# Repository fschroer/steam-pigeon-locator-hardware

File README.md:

# Steam Pigeon locator hardware

KiCad 10 design for the Steam Pigeon rocket locator: an STM32WL5MOC LoRa module with GPS, IMU, barometer, flash, USB-C charging and four deployment channels. Firmware lives in [steam-pigeon-locator](https://github.com/fschroer/steam-pigeon-locator).

## Board at a glance

| Block | Parts |
| --- | --- |
| MCU and radio | STM32WL5MOCH6TR (U5), U.FL antenna (J7), high-power PA configuration |
| GPS | u-blox SAM-M10Q (U2), I2C2 at 0x42 |
| Sensors | ISM6HG256X IMU (U14), MS5611 barometer (U16), MX25L6436F flash (U17), all on SPI2 |
| Power | BQ25185 charger (U18), RT9080-33 LDO (U7), DRV5032 Hall sensor and 74HCS00 latch for magnet on/off |
| USB | USB-C (J1), CH340N serial (U4) |
| Deployment | Arm switch U13 (DMP2021UFDF) driven by DARM, four TPS22950 high-side switches plus PMXB43UNE (DFN1010D-3) low-side return switches (Q4-Q7) on J2 and J4; continuity sense DS1-DS4 on the return side |
| Audio | PAM8904 piezo driver (U11) |

Board size is 54 x 25 mm, 4 layers. The silkscreen carries the board revision (currently `SPL915STM B01`).

## Repository layout

| Path | Contents |
| --- | --- |
| `RocketLocator.kicad_pro`, `.kicad_sch`, `.kicad_pcb` | The design |
| `lib/` | Project-local symbol and footprint libraries |
| `sym-lib-table`, `fp-lib-table` | Project library tables pointing into `lib/` |
| `BOM/RocketLocatorBOM.xlsx` | Purchasing BOM: JLCPCB part numbers, cost, stock and order tracking, plus a JLCPCB upload sheet. Maintained by hand; keep it in step with the schematic |
| `.github/workflows/kicad.yml` | ERC, DRC and fab outputs on every push |

Generated files (Gerbers, drill, BOM, CPL, netlist, PDF) are not committed. CI builds them on every push as a downloadable workflow artifact, and attaches them to a GitHub release when you push a board tag.

## Open design issues

Findings from the 2026-10-15 design review are tracked as GitHub issues. The full write-up is in the [RocketLocator design review](https://claude.ai/code/artifact/725ce922-3286-4f00-98c2-284a111a1c0e).

## Libraries

Non-stock parts live in `lib/` and are registered in the project's `sym-lib-table` and `fp-lib-table` with `${KIPRJMOD}` paths, so a fresh clone opens without any global library setup. Project entries override a global library with the same nickname.

| Library | Contents | Source |
| --- | --- | --- |
| `Custom.kicad_sym`, `Custom.pretty` | Project symbols and footprints | Copied from the personal KiCad 9.0 `Custom` libraries, 2026-10-15 |
| `RT9080-33GJ5.kicad_sym` | RT9080-33 LDO symbol | Extracted from the schematic's embedded symbol cache |
| `STM32WL5MOCH6TR.kicad_sym` | STM32WL5MOC module symbol | Extracted from the schematic's embedded symbol cache |
| `U.FL-R-SMT_01_.kicad_sym` | U.FL receptacle symbol | Extracted from the schematic's embedded symbol cache |

`Custom.pretty` also holds `SOT94P280X100-5N` (U7) and `SOP-8_5.28x5.23mm_P1.27mm` (U17). Their original libraries (`RT9080`, `Package_SO_New`) no longer existed, so they were recovered from the board file, converted back to front-side library form, and the design was relinked to `Custom:`.

When you change a part, edit it in `lib/` (not in your personal library) and commit it with the design change. All 3D models referenced by the footprints come from KiCad's stock 3D library.

## Releasing a board

1. Make sure ERC and DRC are clean.
2. Update the silkscreen revision and date.
3. Commit, then tag with the board revision and order date, for example `git tag B02-2026-11-20 && git push --tags`.
4. Download the Gerber zip, BOM and CPL from the release and upload them to the fab.

## Working copy

Keep the working copy outside Google Drive, OneDrive or Dropbox, because folder sync corrupts the `.git` directory. GitHub is the backup.

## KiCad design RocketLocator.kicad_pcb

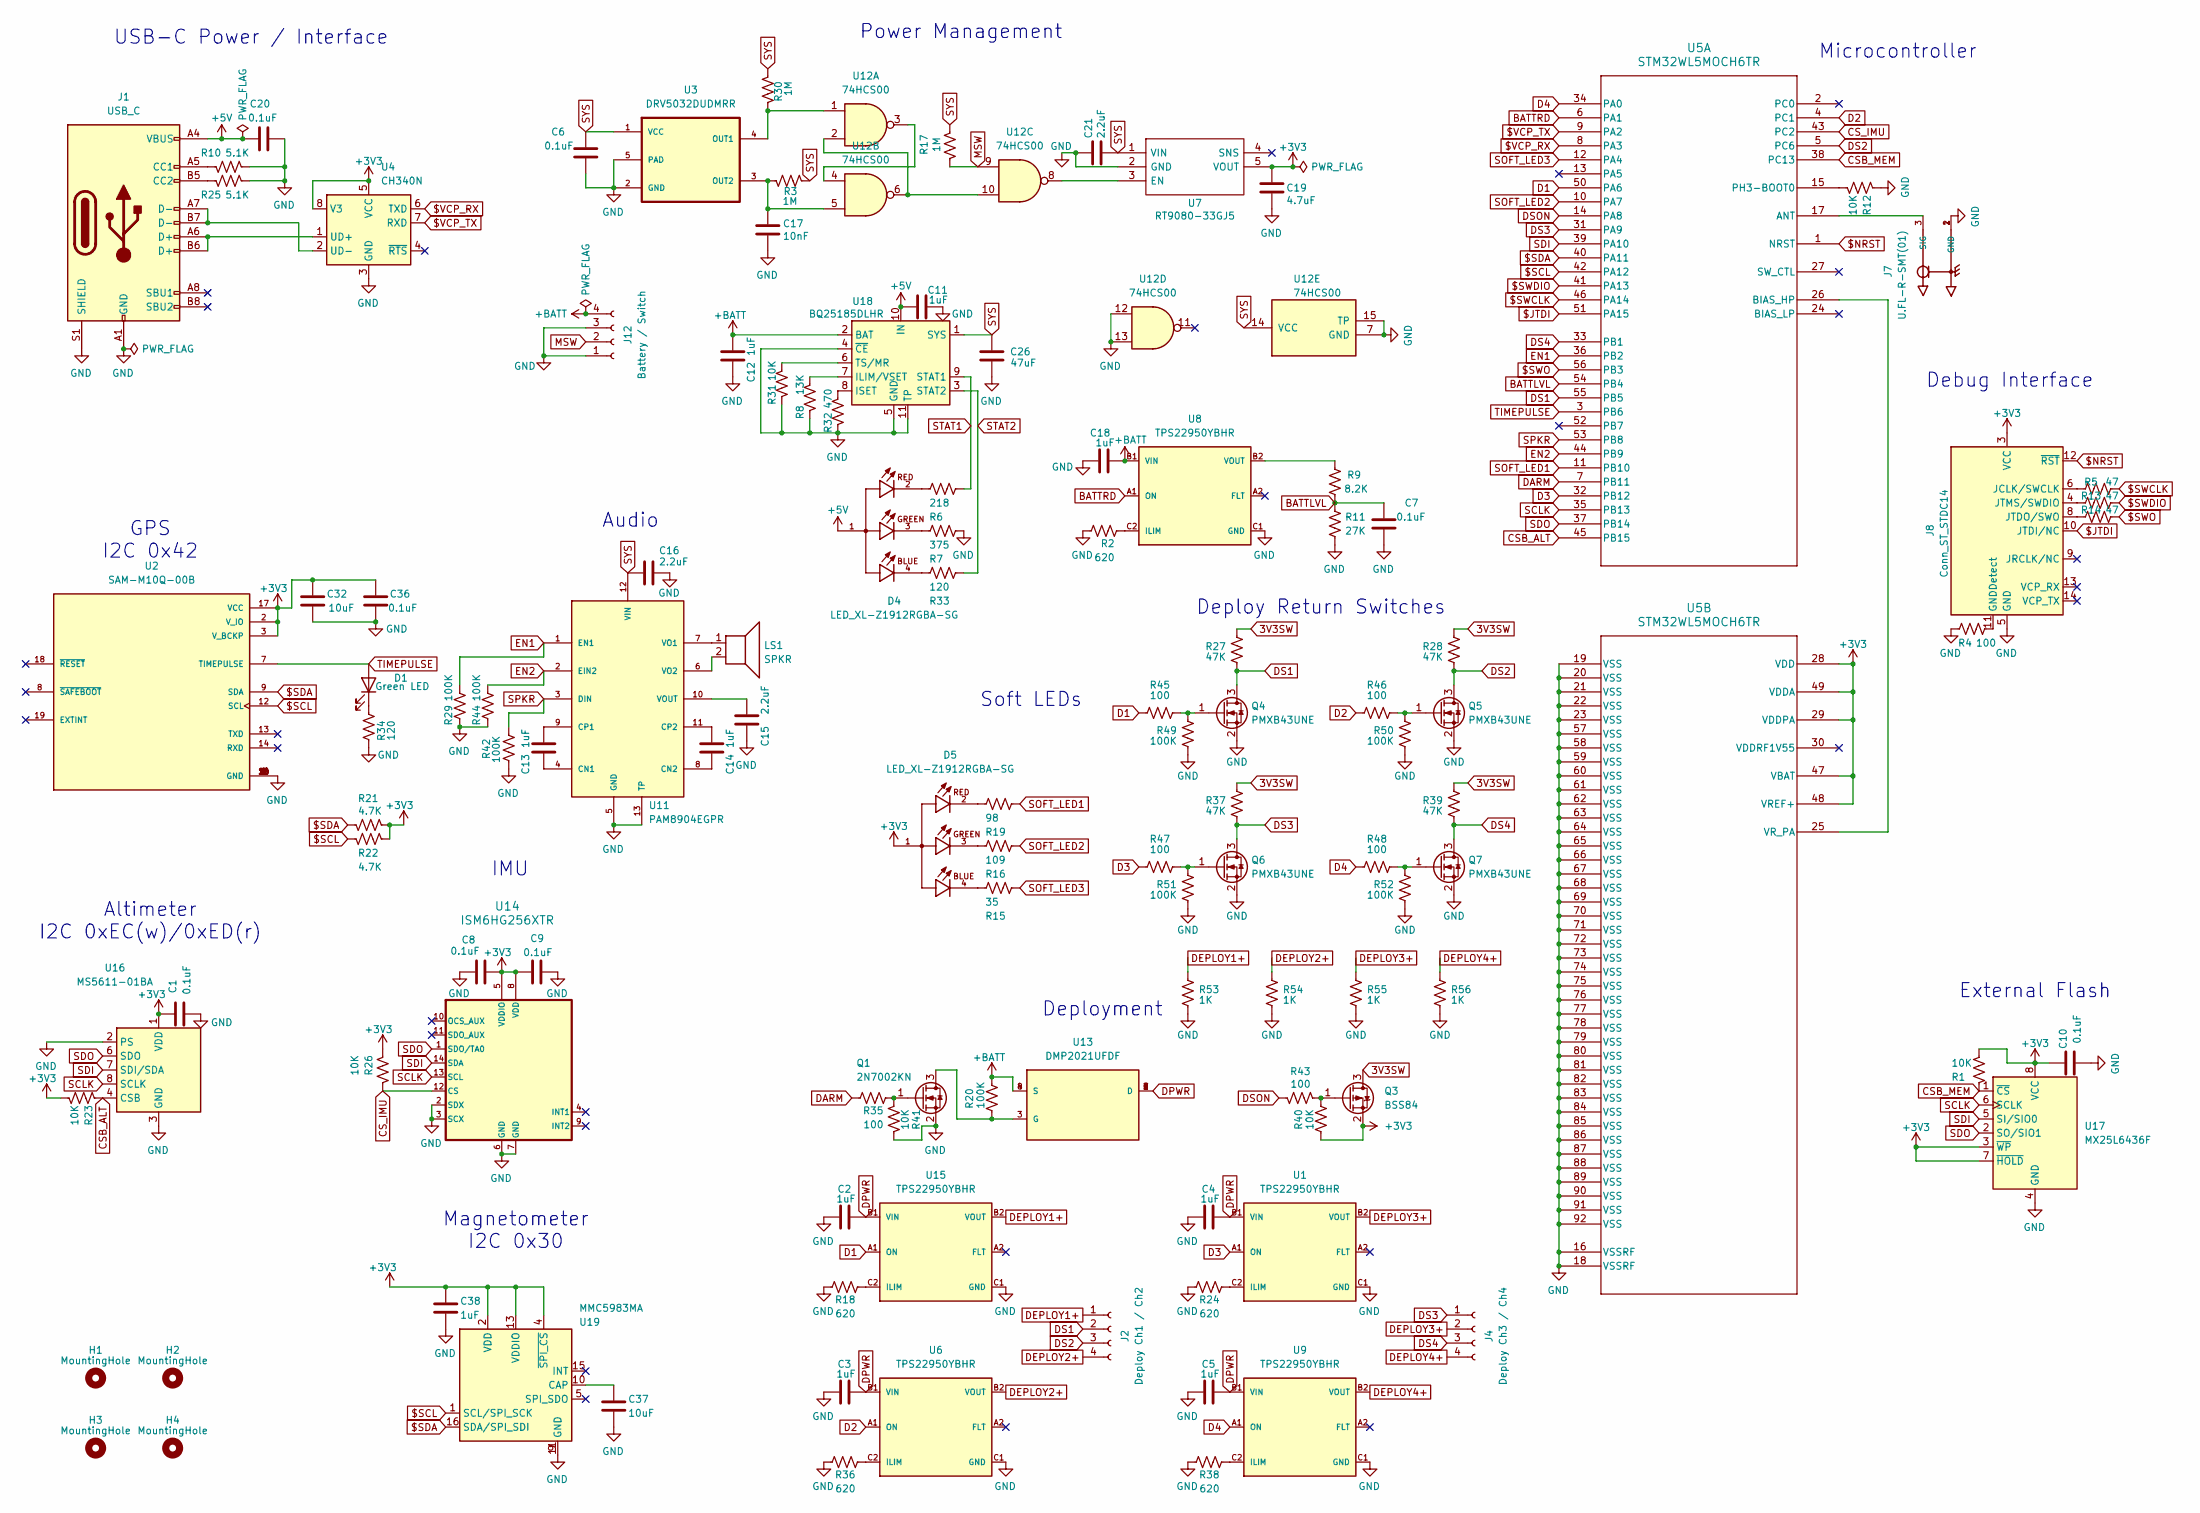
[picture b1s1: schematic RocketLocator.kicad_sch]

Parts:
C1, C6, C7, C8, C9, C10, C20, C36: 0.1uF; C_0402_1005Metric
C2, C3, C4, C5, C11, C12, C13, C14, C18, C38: 1uF; C_0402_1005Metric
C15, C16, C21: 2.2uF; C_0402_1005Metric
C17: 10nF; C_0402_1005Metric
C19: 4.7uF; C_0402_1005Metric
C26: 47uF; C_1206_3216Metric
C32, C37: 10uF; C_0402_1005Metric
D1: Green LED; LED_0402_1005Metric
D4, D5: LED_XL-Z1912RGBA-SG
H1, H2, H3, H4: MountingHole; MountingHole_2.2mm_M2
J1: USB_C; USB_C_Receptacle_Palconn_UTC16-G
J2: Deploy Ch1 / Ch2; PinHeader_1x04_P2.54mm_Vertical
J4: Deploy Ch3 / Ch4; PinHeader_1x04_P2.54mm_Vertical
J7: U.FL-R-SMT(01); HRS_U.FL-R-SMT(01)
J8: Conn_ST_STDC14; SAMTEC_FTR-107-51-G-D
J12: Battery / Switch; PinHeader_1x06_P2.54mm_Vertical_Pos4-5_Empty
LS1: SPKR; PiezoBuzzer
Q1: 2N7002KN; DFN1006-3L
Q3: BSS84; DFN1006-3L
Q4, Q5, Q6, Q7: PMXB43UNE; Nexperia_DFN1010D-3_SOT1215
R1, R12, R23, R26, R31, R40, R41: 10K; R_0402_1005Metric
R2, R18, R24, R36, R38: 620; R_0402_1005Metric
R3, R17, R30: 1M; R_0402_1005Metric
R4, R35, R43, R45, R46, R47, R48: 100; R_0402_1005Metric
R5, R13, R14: 47; R_0402_1005Metric
R6: 218; R_0402_1005Metric
R7: 375; R_0402_1005Metric
R8: 13K; R_0402_1005Metric
R9: 8.2K; R_0402_1005Metric
R10, R25: 5.1K; R_0402_1005Metric
R11: 27K; R_0402_1005Metric
R15: 35; R_0402_1005Metric
R16: 109; R_0402_1005Metric
R19: 98; R_0402_1005Metric
R20, R29, R42, R44, R49, R50, R51, R52: 100K; R_0402_1005Metric
R21, R22: 4.7K; R_0402_1005Metric
R27, R28, R37, R39: 47K; R_0402_1005Metric
R32: 470; R_0402_1005Metric
R33, R34: 120; R_0402_1005Metric
R53, R54, R55, R56: 1K; R_0402_1005Metric
U1, U6, U8, U9, U15: TPS22950YBHR; IC_TPS22950YBHR
U2: SAM-M10Q-00B; XCVR_SAM-M10Q-00B; PARTREV R03
U3: DRV5032DUDMRR; X2SON
U4: CH340N; JEITA_SOIC-8_3.9x4.9mm_P1.27mm
U5: STM32WL5MOCH6TR; LGA-92_10X10_STM
U7: RT9080-33GJ5; SOT94P280X100-5N; Manufacturer_Part_Number RT9080-33GJ5
U11: PAM8904EGPR; W-QFN2020-12-EP(2x2)
U12: 74HCS00; WQFN 14 3.00 mm × 2.50 mm
U13: DMP2021UFDF; Diodes_UDFN2020-6_Type-F
U14: ISM6HG256XTR; U_LGA-14L_2p5X3p0X0p83_STM
U16: MS5611-01BA; LGA-8_3x5mm_P1.25mm
U17: MX25L6436F; SOP-8_5.28x5.23mm_P1.27mm
U18: BQ25185DLHR
U19: MMC5983MA; LGA-16_3x3mm_P0.5mm

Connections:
3V3SW: Q3.3 (D), R27.1, R28.2, R37.1, R39.2
$JTDI: J8.10 (JTDI/NC), U5.51 (PA15)
$NRST: J8.12 (~RST), U5.1 (NRST)
$SCL: R22.2, U2.12 (SCL), U5.42 (PA12), U19.1 (SCL/SPI_SCK)
$SDA: R21.2, U2.9 (SDA), U5.40 (PA11), U19.16 (SDA/SPI_SDI)
$SWCLK: R5.1, U5.46 (PA14)
$SWDIO: R13.1, U5.41 (PA13)
$SWO: R14.1, U5.56 (PB3)
$VCP_RX: U4.6 (TXD), U5.8 (PA3)
$VCP_TX: U4.7 (RXD), U5.9 (PA2)
+3V3: C1.1, C8.2, C9.1, C10.1, C19.1, C32.1, C36.2, C38.1, D5.1, J8.3 (VCC), Q3.2 (S), R1.2, R21.1, R22.1, R23.2, R26.2, R40.2, U2.2 (V_IO), U2.3 (V_BCKP), U2.17 (VCC), U4.5 (VCC), U4.8 (V3), U5.28 (VDD), U5.29 (VDDPA), U5.47 (VBAT), U5.48 (VREF+), U5.49 (VDDA), U7.5 (VOUT), U14.5 (VDDIO), U14.8 (VDD), U16.1 (VDD), U17.3 (~WP), U17.7 (~HOLD), U17.8 (VCC), U19.2 (VDD), U19.4 (~SPI_CS), U19.13 (VDDIO)
+5V: C11.1, C20.1, D4.1, J1.A4 (VBUS), J1.A9 (VBUS), J1.B4 (VBUS), J1.B9 (VBUS), U18.10 (IN)
+BATT: C12.2, C18.2, J12.4, R20.1, U8.B1 (VIN), U13.4 (S), U13.8 (S), U18.2 (BAT)
BATTLVL: C7.1, R9.1, R11.1, U5.54 (PB4)
BATTRD: U5.6 (PA1), U8.A1 (ON)
CSB_ALT: R23.1, U5.45 (PB15), U16.4 (CSB), U16.5 (CSB)
CSB_MEM: R1.1, U5.38 (PC13), U17.1 (~CS)
CS_IMU: R26.1, U5.43 (PC2), U14.12 (CS)
D1: R45.2, U5.50 (PA6), U15.A1 (ON)
D2: R46.2, U5.4 (PC1), U6.A1 (ON)
D3: R47.2, U1.A1 (ON), U5.32 (PB12)
D4: R48.2, U5.34 (PA0), U9.A1 (ON)
DARM: R35.1, U5.7 (PB11)
DEPLOY1+: J2.1, R53.1, U15.B2 (VOUT)
DEPLOY2+: J2.4, R54.1, U6.B2 (VOUT)
DEPLOY3+: J4.2, R55.1, U1.B2 (VOUT)
DEPLOY4+: J4.4, R56.1, U9.B2 (VOUT)
DPWR: C2.2, C3.2, C4.2, C5.2, U1.B1 (VIN), U6.B1 (VIN), U9.B1 (VIN), U13.1 (D), U13.2 (D), U13.5 (D), U13.6 (D), U13.7 (D), U15.B1 (VIN)
DS1: J2.2, Q4.3 (D), R27.2, U5.55 (PB5)
DS2: J2.3, Q5.3 (D), R28.1, U5.5 (PC6)
DS3: J4.1, Q6.3 (D), R37.2, U5.31 (PA9)
DS4: J4.3, Q7.3 (D), R39.1, U5.33 (PB1)
DSON: R43.1, U5.14 (PA8)
EN1: R29.2, U5.36 (PB2), U11.1 (EN1)
EN2: R44.2, U5.44 (PB9), U11.2 (EIN2)
GND: C1.2, C2.1, C3.1, C4.1, C5.1, C6.2, C7.2, C8.1, C9.2, C10.2, C11.2, C12.1, C15.1, C16.1, C17.1, C18.1, C19.2, C20.2, C21.1, C26.1, C32.2, C36.1, C37.2, C38.2, J1.A1 (GND), J1.A12 (GND), J1.B1 (GND), J1.B12 (GND), J1.S1 (SHIELD), J7.1 (GND), J7.2 (GND), J8.5 (GND), J8.7 (GND), J12.1, J12.3, Q1.2 (S), Q4.2 (S), Q5.2 (S), Q6.2 (S), Q7.2 (S), R2.1, R4.2, R7.1, R8.1, R10.2, R11.2, R12.1, R18.1, R24.1, R25.2, R29.1, R31.1, R32.1, R34.1, R36.1, R38.1, R41.2, R42.1, R44.1, R49.2, R50.2, R51.2, R52.2, R53.2, R54.2, R55.2, R56.2, U1.C1 (GND), U2.1 (GND), U2.4 (GND), U2.5 (GND), U2.6 (GND), U2.10 (GND), U2.11 (GND), U2.15 (GND), U2.16 (GND), U2.20 (GND), U3.2 (GND), U3.5 (PAD), U4.3 (GND), U5.16 (VSSRF), U5.18 (VSSRF), U5.19 (VSS), U5.20 (VSS), U5.21 (VSS), U5.22 (VSS), U5.23 (VSS), U5.57 (VSS), U5.58 (VSS), U5.59 (VSS), U5.60 (VSS), U5.61 (VSS), U5.62 (VSS), U5.63 (VSS), U5.64 (VSS), U5.65 (VSS), U5.66 (VSS), U5.67 (VSS), U5.68 (VSS), U5.69 (VSS), U5.70 (VSS), U5.71 (VSS), U5.72 (VSS), U5.73 (VSS), U5.74 (VSS), U5.75 (VSS), U5.76 (VSS), U5.77 (VSS), U5.78 (VSS), U5.79 (VSS), U5.80 (VSS), U5.81 (VSS), U5.82 (VSS), U5.83 (VSS), U5.84 (VSS), U5.85 (VSS), U5.86 (VSS), U5.87 (VSS), U5.88 (VSS), U5.89 (VSS), U5.90 (VSS), U5.91 (VSS), U5.92 (VSS), U6.C1 (GND), U7.2 (GND), U8.C1 (GND), U9.C1 (GND), U11.5 (GND), U11.13 (TP), U12.7 (GND), U12.12, U12.13, U12.15 (TP), U14.2 (SDX), U14.3 (SCX), U14.6 (GND), U14.7 (GND), U15.C1 (GND), U16.2 (PS), U16.3 (GND), U17.4 (GND), U18.4 (~CE), U18.5 (GND), U18.11 (TP), U19.9 (GND), U19.11 (GND)
MSW: J12.2, R17.2, U12.9
unnamed: D1.1 (K), R34.2
unnamed: D4.2, R6.2
unnamed: D4.3, R7.2
unnamed: D4.4, R33.2
unnamed: D5.2, R19.2
unnamed: D5.3, R16.2
unnamed: D5.4, R15.2
unnamed: J1.A5 (CC1), R10.1
unnamed: J1.B5 (CC2), R25.1
unnamed: J7.3 (SIG), U5.17 (ANT)
unnamed: J8.11 (GNDDetect), R4.1
unnamed: J8.6 (JCLK/SWCLK), R5.2
unnamed: J8.8 (JTDO/SWO), R14.2
unnamed: J8.4 (JTMS/SWDIO), R13.2
unnamed: Q1.3 (D), R20.2, U13.3 (G)
unnamed: Q1.1 (G), R35.2, R41.1
unnamed: Q3.1 (G), R40.1, R43.2
unnamed: Q4.1 (G), R45.1, R49.1
unnamed: Q5.1 (G), R46.1, R50.1
unnamed: Q6.1 (G), R47.1, R51.1
unnamed: Q7.1 (G), R48.1, R52.1
unnamed: R24.2, U1.C2 (ILIM)
unnamed: R30.2, U3.4 (OUT1), U12.1
unnamed: C17.2, R3.2, U3.3 (OUT2), U12.5
unnamed: J1.A6 (D+), J1.B6 (D+), U4.1 (UD+)
unnamed: J1.A7 (D-), J1.B7 (D-), U4.2 (UD-)
unnamed: U5.25 (VR_PA), U5.26 (BIAS_HP)
unnamed: R12.2, U5.15 (PH3-BOOT0)
unnamed: R36.2, U6.C2 (ILIM)
unnamed: U7.3 (EN), U12.8
unnamed: R2.2, U8.C2 (ILIM)
unnamed: R9.2, U8.B2 (VOUT)
unnamed: R38.2, U9.C2 (ILIM)
unnamed: C13.1, U11.4 (CN1)
unnamed: C14.1, U11.8 (CN2)
unnamed: C13.2, U11.9 (CP1)
unnamed: C14.2, U11.11 (CP2)
unnamed: LS1.1, U11.7 (VO1)
unnamed: LS1.2, U11.6 (VO2)
unnamed: C15.2, U11.10 (VOUT)
unnamed: U12.3, U12.4
unnamed: U12.2, U12.6, U12.10
unnamed: R18.2, U15.C2 (ILIM)
unnamed: R8.2, U18.7 (ILIM/VSET)
unnamed: R32.2, U18.8 (ISET)
unnamed: R31.2, U18.6 (TS/MR)
unnamed: C37.1, U19.10 (CAP)
SCLK: U5.35 (PB13), U14.13 (SCL), U16.8 (SCLK), U17.6 (SCLK)
SDI: U5.39 (PA10), U14.14 (SDA), U16.7 (SDI/SDA), U17.5 (SI/SIO0)
SDO: U5.37 (PB14), U14.1 (SDO/TA0), U16.6 (SDO), U17.2 (SO/SIO1)
SOFT_LED1: R19.1, U5.11 (PB10)
SOFT_LED2: R16.1, U5.10 (PA7)
SOFT_LED3: R15.1, U5.12 (PA4)
SPKR: R42.2, U5.53 (PB8), U11.3 (DIN)
STAT1: R6.1, U18.9 (STAT1)
STAT2: R33.1, U18.3 (STAT2)
SYS: C6.1, C16.2, C21.2, C26.2, R3.1, R17.1, R30.1, U3.1 (VCC), U7.1 (VIN), U11.12 (VIN), U12.14 (VCC), U18.1 (SYS)
TIMEPULSE: D1.2 (A), U2.7 (TIMEPULSE), U5.3 (PB6)

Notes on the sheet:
Deployment
Debug Interface
Deploy Return Switches
Soft LEDs
USB-C Power / Interface
Audio
GPS I2C 0x42
Magnetometer I2C 0x30
Power Management
External Flash
Altimeter I2C 0xEC(w)/0xED(r)
Microcontroller
IMU

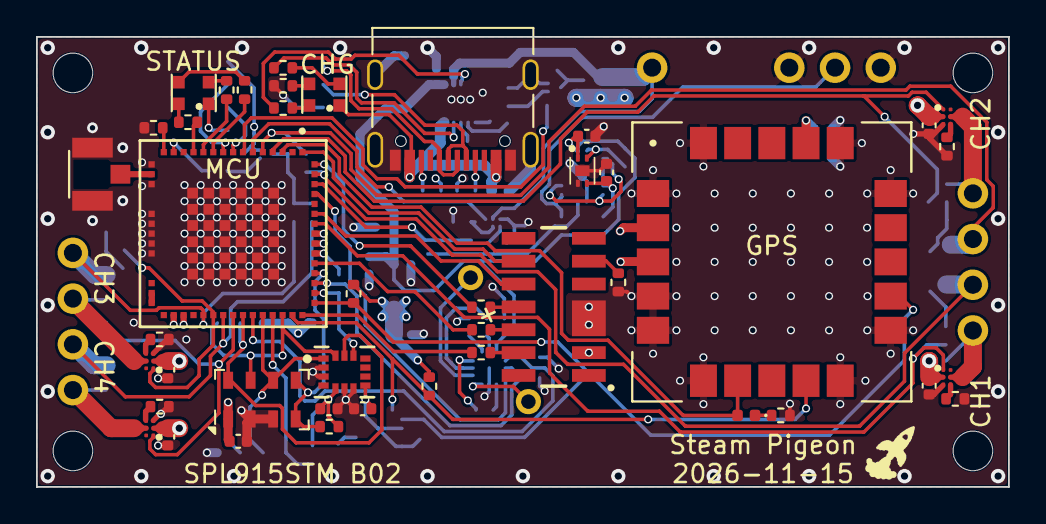
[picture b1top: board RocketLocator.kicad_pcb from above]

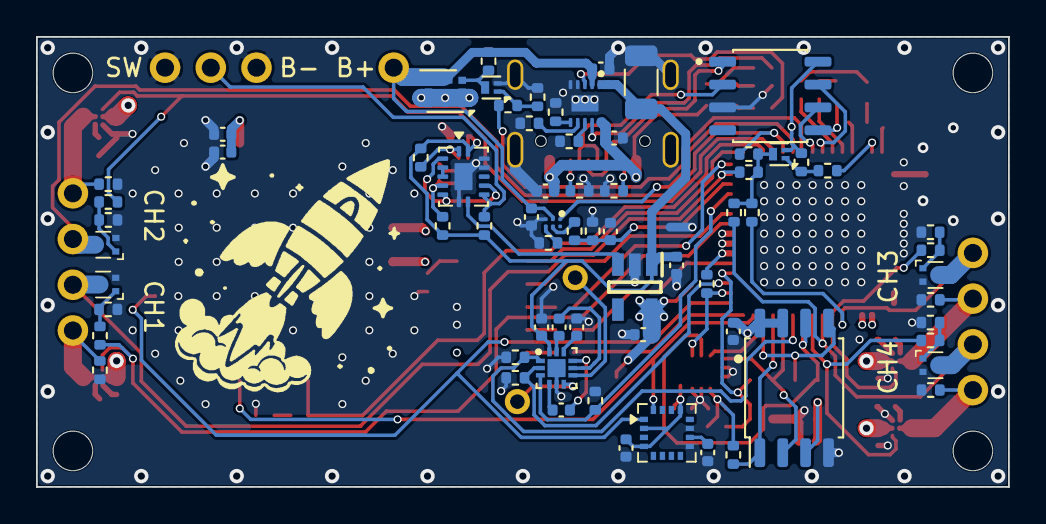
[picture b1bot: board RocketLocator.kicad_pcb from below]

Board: 4 copper layers, 54.0 x 25.0 mm, 122 parts (70 on the bottom side), 95 nets.

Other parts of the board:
G1: SteamPigeon_Logo_13mm
G2: SteamPigeon_Logo_3mm

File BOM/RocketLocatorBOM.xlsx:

Comment | Designator | Footprint | JLCPCB Part #（optional）
2.2uF | C15,C16,C21 | C_0402_1005Metric | C307418
10nF | C17 | C_0402_1005Metric | C15195
10uF | C32,C37 | C_0402_1005Metric | C15525
1uF | C2,C3,C4,C5,C11,C12,C13,C14,C18,C38 | C_0402_1005Metric | C52923
0.1uF | C1,C6,C7,C8,C9,C10,C20,C36 | C_0402_1005Metric | C1525
47uF | C26 | C_1206_3216Metric | C96123
4.7uF | C19 | C_0402_1005Metric | C368809
Green LED | D1 | LED_0402_1005Metric | C965794
LED_XL-Z1912RGBA-SG | D4,D5 | LED_XL-Z1912RGBA-SG | C22461785
USB_C | J1 | USB_C_Receptacle_Palconn_UTC16-G | C2927038
U.FL-R-SMT(01) | J7 | HRS_U.FL-R-SMT(01) | C5137195
2N7002KN | Q1 | DFN1006-3L | C49009905
BSS84 | Q3 | DFN1006-3L | C42394022
PMXB43UNE | Q4,Q5,Q6,Q7 | Nexperia_DFN1010D-3_SOT1215 | C547273
5.1K | R10,R25 | R_0402_1005Metric | C294638
27K 0.1% | R11 | R_0402_1005Metric | C25207446
33 | R15 | R_0402_1005Metric | C25105
620 | R2,R18,R24,R36,R38 | R_0402_1005Metric | C4961
1M | R3,R17,R30 | R_0402_1005Metric | C26083
470 | R32 | R_0402_1005Metric | C25117
120 | R33,R34 | R_0402_1005Metric | C25079
47K | R27,R28,R37,R39 | R_0402_1005Metric | C25792
10K | R1,R12,R23,R26,R31,R40,R41 | R_0402_1005Metric | C25531
4.7K | R21,R22 | R_0402_1005Metric | C25900
100 | R4,R16,R19,R35,R43,R45,R46,R47,R48 | R_0402_1005Metric | C25076
47 | R5,R13,R14 | R_0402_1005Metric | C25118
220 | R6 | R_0402_1005Metric | C25091
374 | R7 | R_0402_1005Metric | C48971914
13K | R8 | R_0402_1005Metric | C25754
8.2K 0.1% | R9 | R_0402_1005Metric | C24265089
100K | R20,R29,R42,R44,R49,R50,R51,R52 | R_0402_1005Metric | C25741
1K | R53,R54,R55,R56 | R_0402_1005Metric | C11702
TPS22950YBHR | U1,U6,U8,U9,U15 | IC_TPS22950YBHR | C3230039
PAM8904EGPR | U11 | W-QFN2020-12-EP(2x2) | C510550
SN74HCS00BQA-Q1 | U12 | WQFN 14 3.00 mm × 2.50 mm | C4469587
DMP2021UFDF | U13 | Diodes_UDFN2020-6_Type-F | C151459
ISM6HG256XTR | U14 | U_LGA-14L_2p5X3p0X0p83_STM | C51931514
MS5611-01BA | U16 | LGA-8_3x5mm_P1.25mm | C15639
MX25L6436F | U17 | SOP-8_5.28x5.23mm_P1.27mm | C2830754
BQ25185DLHR | U18 | BQ25185DLHR | C19725033
SAM-M10Q-00B | U2 | XCVR_SAM-M10Q-00B | C5443880
DRV5032DUDMRR | U3 | X2SON | C2152495
CH340N | U4 | JEITA_SOIC-8_3.9x4.9mm_P1.27mm | C2977777
STM32WL5MOCH6TR | U5 | LGA-92_10X10_STM | C22363244
RT9080-33GJ5 | U7 | SOT94P280X100-5N | C841192
MMC5983MA | U19 | LGA-16_3x3mm_P0.5mm | C404329
